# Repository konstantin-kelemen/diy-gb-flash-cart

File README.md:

# FPGA-картридж с Flash-памятью для Game Boy

Экспериментальный USB-программируемый картридж для оригинального Game Boy:
MachXO2-1200HC, NOR Flash MX29LV320E (4 МБ), F-RAM FM28V100 (128 КБ),
RP2040-Zero и преобразователи уровней SN74LVC8T245.

## С чего начать

- [Состояние проекта](docs/STATUS.md) — что реализовано и что проверено.
- [План работ](docs/ROADMAP.md) — следующие этапы и критерии готовности.
- [Документация](docs/README.md) — архитектура, испытания и приоритет источников.
- [Первый обмен USB/SPI](docs/SPI_BRINGUP.md) — подключение стенда и протокол.
- [Запись .gb во Flash](docs/PROGRAMMER.md) — чтение, запись и сравнение ROM.

## Структура репозитория

| Каталог | Содержимое |
|---|---|
| [docs/](docs/README.md) | Проектная документация и журнал испытаний |
| [hardware/](hardware/README.md) | Схемы, PCB и локальные библиотеки KiCad |
| [fpga/](fpga/README.md) | RTL, ограничения, тесты и проект Diamond |
| [firmware/](firmware/README.md) | Прошивки RP2040: SPI-тест и программатор |
| [host/](host/README.md) | Утилита записи и проверки Flash |
| [references/](references/README.md) | Техническая документация и сторонние материалы |
| [releases/](releases/README.md) | Сохранённые сборки и производственные файлы |

Электрические соединения определяет [схема картриджа](hardware/cartridge/cartridge.kicad_sch);
правила сверки приведены в [документации](docs/README.md#приоритет-источников).
Перед работой с памятью см. [режимы и требования безопасности](docs/ARCHITECTURE.md#режимы-работы).

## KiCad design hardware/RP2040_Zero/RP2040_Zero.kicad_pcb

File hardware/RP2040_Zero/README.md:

# Реконструкция Waveshare RP2040-Zero

Отдельный проект KiCad 10: схема и PCB модуля, локальные символы,
посадочные места и таблицы библиотек. `RP2040_Zero.pdf` — сохранённый
исходный материал; `FOOTPRINT_AUDIT.md` — подробности выбора посадочных мест.

Открывать `RP2040_Zero.kicad_pro`. Для стандартных компонентов нужны штатные
библиотеки KiCad. Проект не заменяет основную схему картриджа.

У L1 посадочное место намеренно не назначено: нумерация выводов
WS2812B-2020 расходится с исходной схемой; требуется сверка установленного LED.
P1/P2/P3 обозначают контактные площадки самой платы, а не отдельные разъёмы;
их геометрия должна быть задана при разводке.

Источник схемы: https://files.waveshare.com/upload/4/4c/RP2040_Zero.pdf

Готовность к производству
и результаты ERC/DRC этим проектом не подтверждаются.

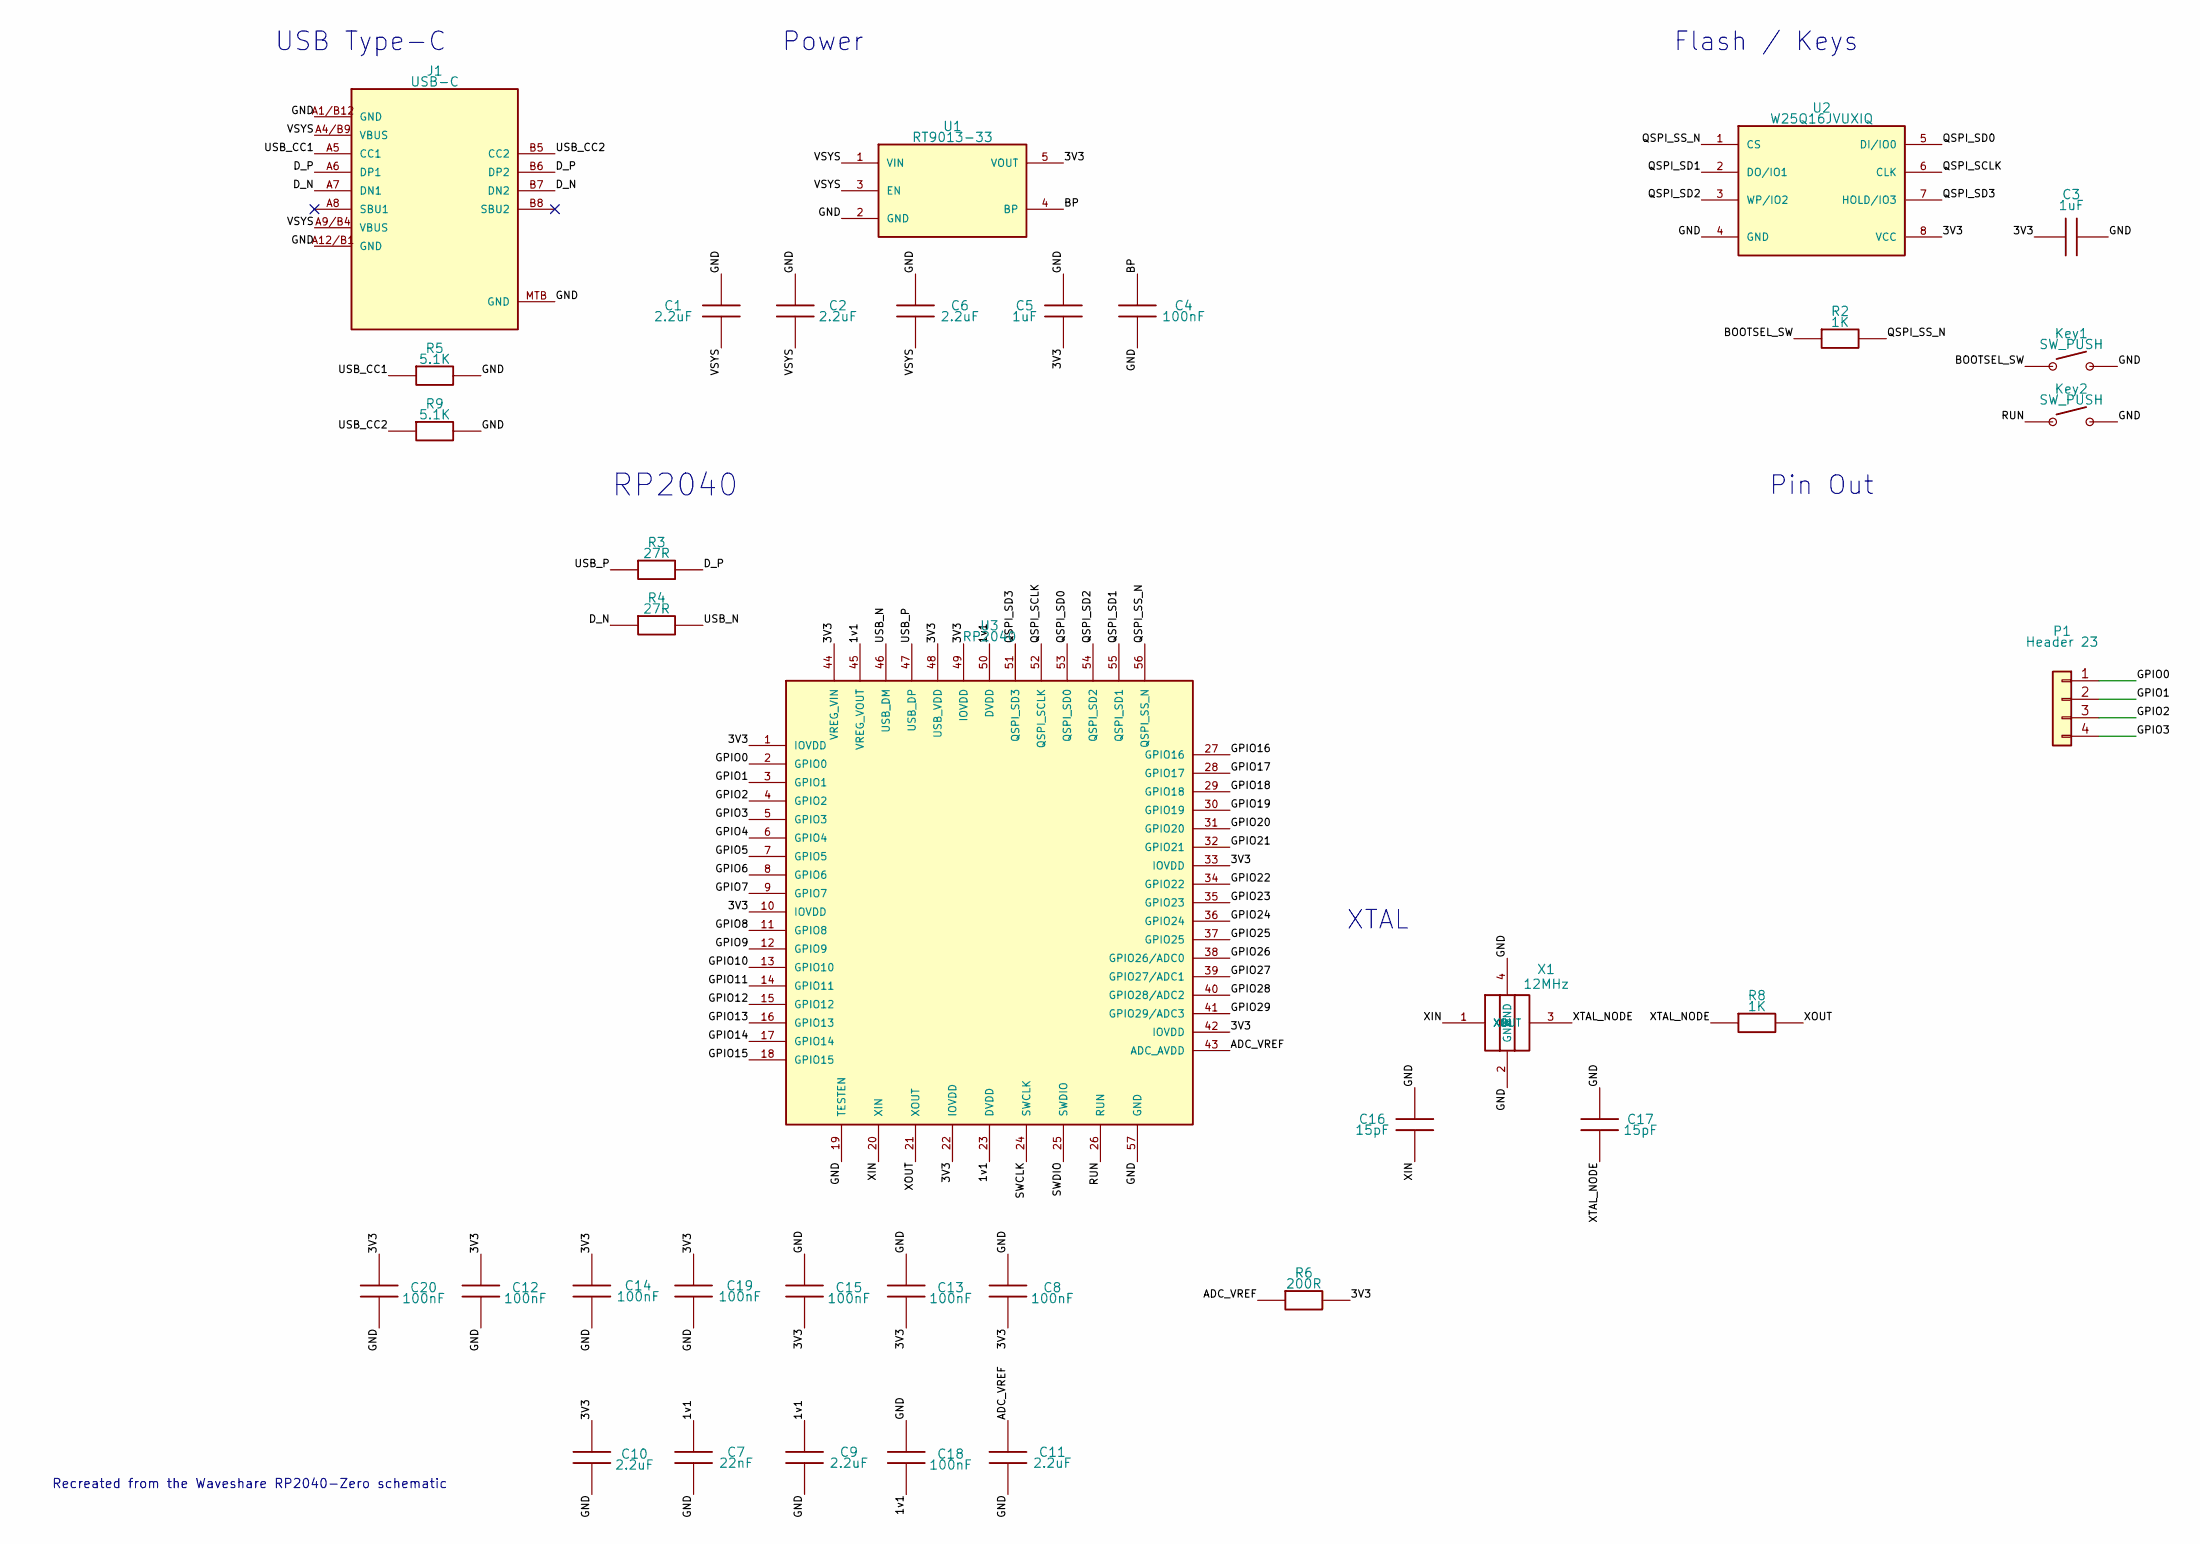
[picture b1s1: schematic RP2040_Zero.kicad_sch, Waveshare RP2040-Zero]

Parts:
C1, C2, C6, C9, C10, C11: 2.2uF; C_0201_0603Metric
C3, C5: 1uF; C_0201_0603Metric
C4, C8, C12, C13, C14, C15, C18, C19, C20: 100nF; C_0201_0603Metric
C7: 22nF; C_0201_0603Metric
C16, C17: 15pF; C_0201_0603Metric
J1: USB-C; USB_C_HRO_TYPE-C-31-M-12_Waveshare
Key1, Key2: SW_PUSH; SW_Tactile_4.5x4.5mm_PhotoMatched
P1: Header 23; PinSocket_1x04_P2.54mm_Vertical
R2, R8: 1K; R_0201_0603Metric
R3, R4: 27R; R_0201_0603Metric
R5, R9: 5.1K; R_0201_0603Metric
R6: 200R; R_0201_0603Metric
U1: RT9013-33; SOT-23-5
U2: W25Q16JVUXIQ; W25Q16JVUXIQ_USON-8_2x3mm
U3: RP2040; QFN-56-1EP_7x7mm_P0.4mm_EP3.2x3.2mm
X1: 12MHz; Crystal_SMD_2520-4Pin_2.5x2.0mm

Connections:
/1v1: C7.1, C9.1, C18.2, U3.23 (DVDD), U3.45 (VREG_VOUT), U3.50 (DVDD)
/3V3: C3.1, C5.2, C8.2, C10.1, C12.1, C13.2, C14.1, C15.2, C19.1, C20.1, R6.2, U1.5 (VOUT), U2.8 (VCC), U3.1 (IOVDD), U3.10 (IOVDD), U3.22 (IOVDD), U3.33 (IOVDD), U3.42 (IOVDD), U3.44 (VREG_VIN), U3.48 (USB_VDD), U3.49 (IOVDD)
/ADC_VREF: C11.1, R6.1, U3.43 (ADC_AVDD)
/BOOTSEL_SW: Key1.1, R2.1
/BP: C4.1, U1.4 (BP)
/D_N: J1.A7 (DN1), J1.B7 (DN2), R4.1
/D_P: J1.A6 (DP1), J1.B6 (DP2), R3.2
/GND: C1.1, C2.1, C3.2, C4.2, C5.1, C6.1, C7.2, C8.1, C9.2, C10.2, C11.2, C12.2, C13.1, C14.2, C15.1, C16.1, C17.1, C18.1, C19.2, C20.2, J1.A1/B12 (GND), J1.A12/B1 (GND), J1.MTB (GND), Key1.2, Key2.2, R5.2, R9.2, U1.2 (GND), U2.4 (GND), U3.19 (TESTEN), U3.57 (GND), X1.2 (GND), X1.4 (GND)
/GPIO0: P1.1, U3.2 (GPIO0)
/GPIO1: P1.2, U3.3 (GPIO1)
/GPIO2: P1.3, U3.4 (GPIO2)
/GPIO3: P1.4, U3.5 (GPIO3)
/GPIO4: U3.6 (GPIO4)
/GPIO5: U3.7 (GPIO5)
/GPIO6: U3.8 (GPIO6)
/GPIO7: U3.9 (GPIO7)
/GPIO8: U3.11 (GPIO8)
/GPIO9: U3.12 (GPIO9)
/GPIO10: U3.13 (GPIO10)
/GPIO11: U3.14 (GPIO11)
/GPIO12: U3.15 (GPIO12)
/GPIO13: U3.16 (GPIO13)
/GPIO14: U3.17 (GPIO14)
/GPIO15: U3.18 (GPIO15)
/GPIO16: U3.27 (GPIO16)
/GPIO17: U3.28 (GPIO17)
/GPIO18: U3.29 (GPIO18)
/GPIO19: U3.30 (GPIO19)
/GPIO20: U3.31 (GPIO20)
/GPIO21: U3.32 (GPIO21)
/GPIO22: U3.34 (GPIO22)
/GPIO23: U3.35 (GPIO23)
/GPIO24: U3.36 (GPIO24)
/GPIO25: U3.37 (GPIO25)
/GPIO26: U3.38 (GPIO26/ADC0)
/GPIO27: U3.39 (GPIO27/ADC1)
/GPIO28: U3.40 (GPIO28/ADC2)
/GPIO29: U3.41 (GPIO29/ADC3)
/QSPI_SCLK: U2.6 (CLK), U3.52 (QSPI_SCLK)
/QSPI_SD0: U2.5 (DI/IO0), U3.53 (QSPI_SD0)
/QSPI_SD1: U2.2 (DO/IO1), U3.55 (QSPI_SD1)
/QSPI_SD2: U2.3 (WP/IO2), U3.54 (QSPI_SD2)
/QSPI_SD3: U2.7 (HOLD/IO3), U3.51 (QSPI_SD3)
/QSPI_SS_N: R2.2, U2.1 (CS), U3.56 (QSPI_SS_N)
/RUN: Key2.1, U3.26 (RUN)
/SWCLK: U3.24 (SWCLK)
/SWDIO: U3.25 (SWDIO)
/USB_CC1: J1.A5 (CC1), R5.1
/USB_CC2: J1.B5 (CC2), R9.1
/USB_N: R4.2, U3.46 (USB_DM)
/USB_P: R3.1, U3.47 (USB_DP)
/VSYS: C1.2, C2.2, C6.2, J1.A4/B9 (VBUS), J1.A9/B4 (VBUS), U1.1 (VIN), U1.3 (EN)
/XIN: C16.2, U3.20 (XIN), X1.1 (XIN)
/XOUT: R8.2, U3.21 (XOUT)
/XTAL_NODE: C17.2, R8.1, X1.3 (XOUT)

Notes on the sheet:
Pin Out
Recreated from the Waveshare RP2040-Zero schematic
XTAL
Flash / Keys
Power
RP2040
USB Type-C

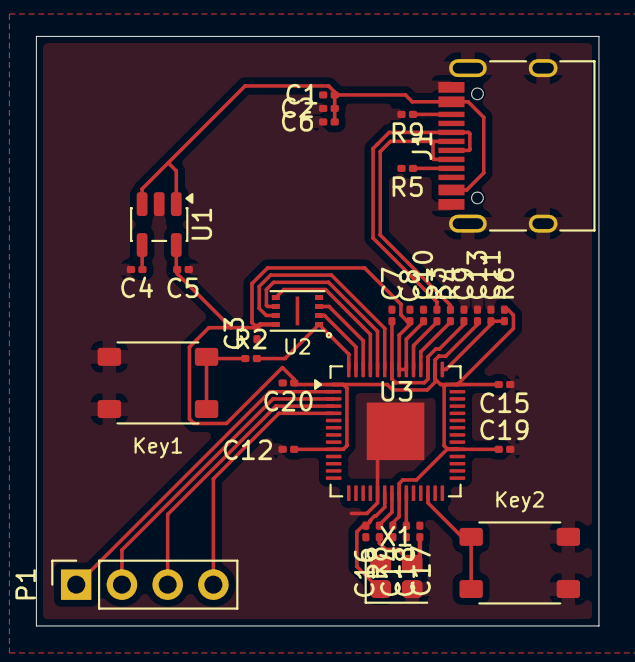
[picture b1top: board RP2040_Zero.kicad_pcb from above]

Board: 2 copper layers, 31.2 x 32.8 mm, 35 parts (0 on the bottom side), 27 nets.

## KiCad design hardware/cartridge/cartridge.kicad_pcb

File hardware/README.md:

# Аппаратная часть

## Проекты

- `breakout/` — разведённая отладочная плата с производственным архивом.
- `cartridge/` — основная схема картриджа и PCB. Состояние разводки — в
  [STATUS.md](../docs/STATUS.md).

- `cartridge/power_mux.kicad_sch` — схема питания; `power_mux_board.kicad_pcb` и
  `power_mux_gerbers/` — отдельная плата и производственные файлы в работе.
- [RP2040_Zero/](RP2040_Zero/README.md) — реконструкция модуля RP2040-Zero.

## Открытие в KiCad

Открывайте `cartridge/cartridge.kicad_pro` или `breakout/breakout.kicad_pro`.
Локальные библиотеки и 3D-модели картриджа хранятся рядом с проектом;
`fp-lib-table` использует пути относительно `${KIPRJMOD}`.
Для стандартных компонентов также нужны штатные библиотеки KiCad.

В `cartridge/sym-lib-table` заданы конкретные файлы локальных символов.

Перед выпуском аппаратной ревизии необходимо выполнить ERC/DRC и сверить LPF с
назначением выводов символа FPGA в схеме.

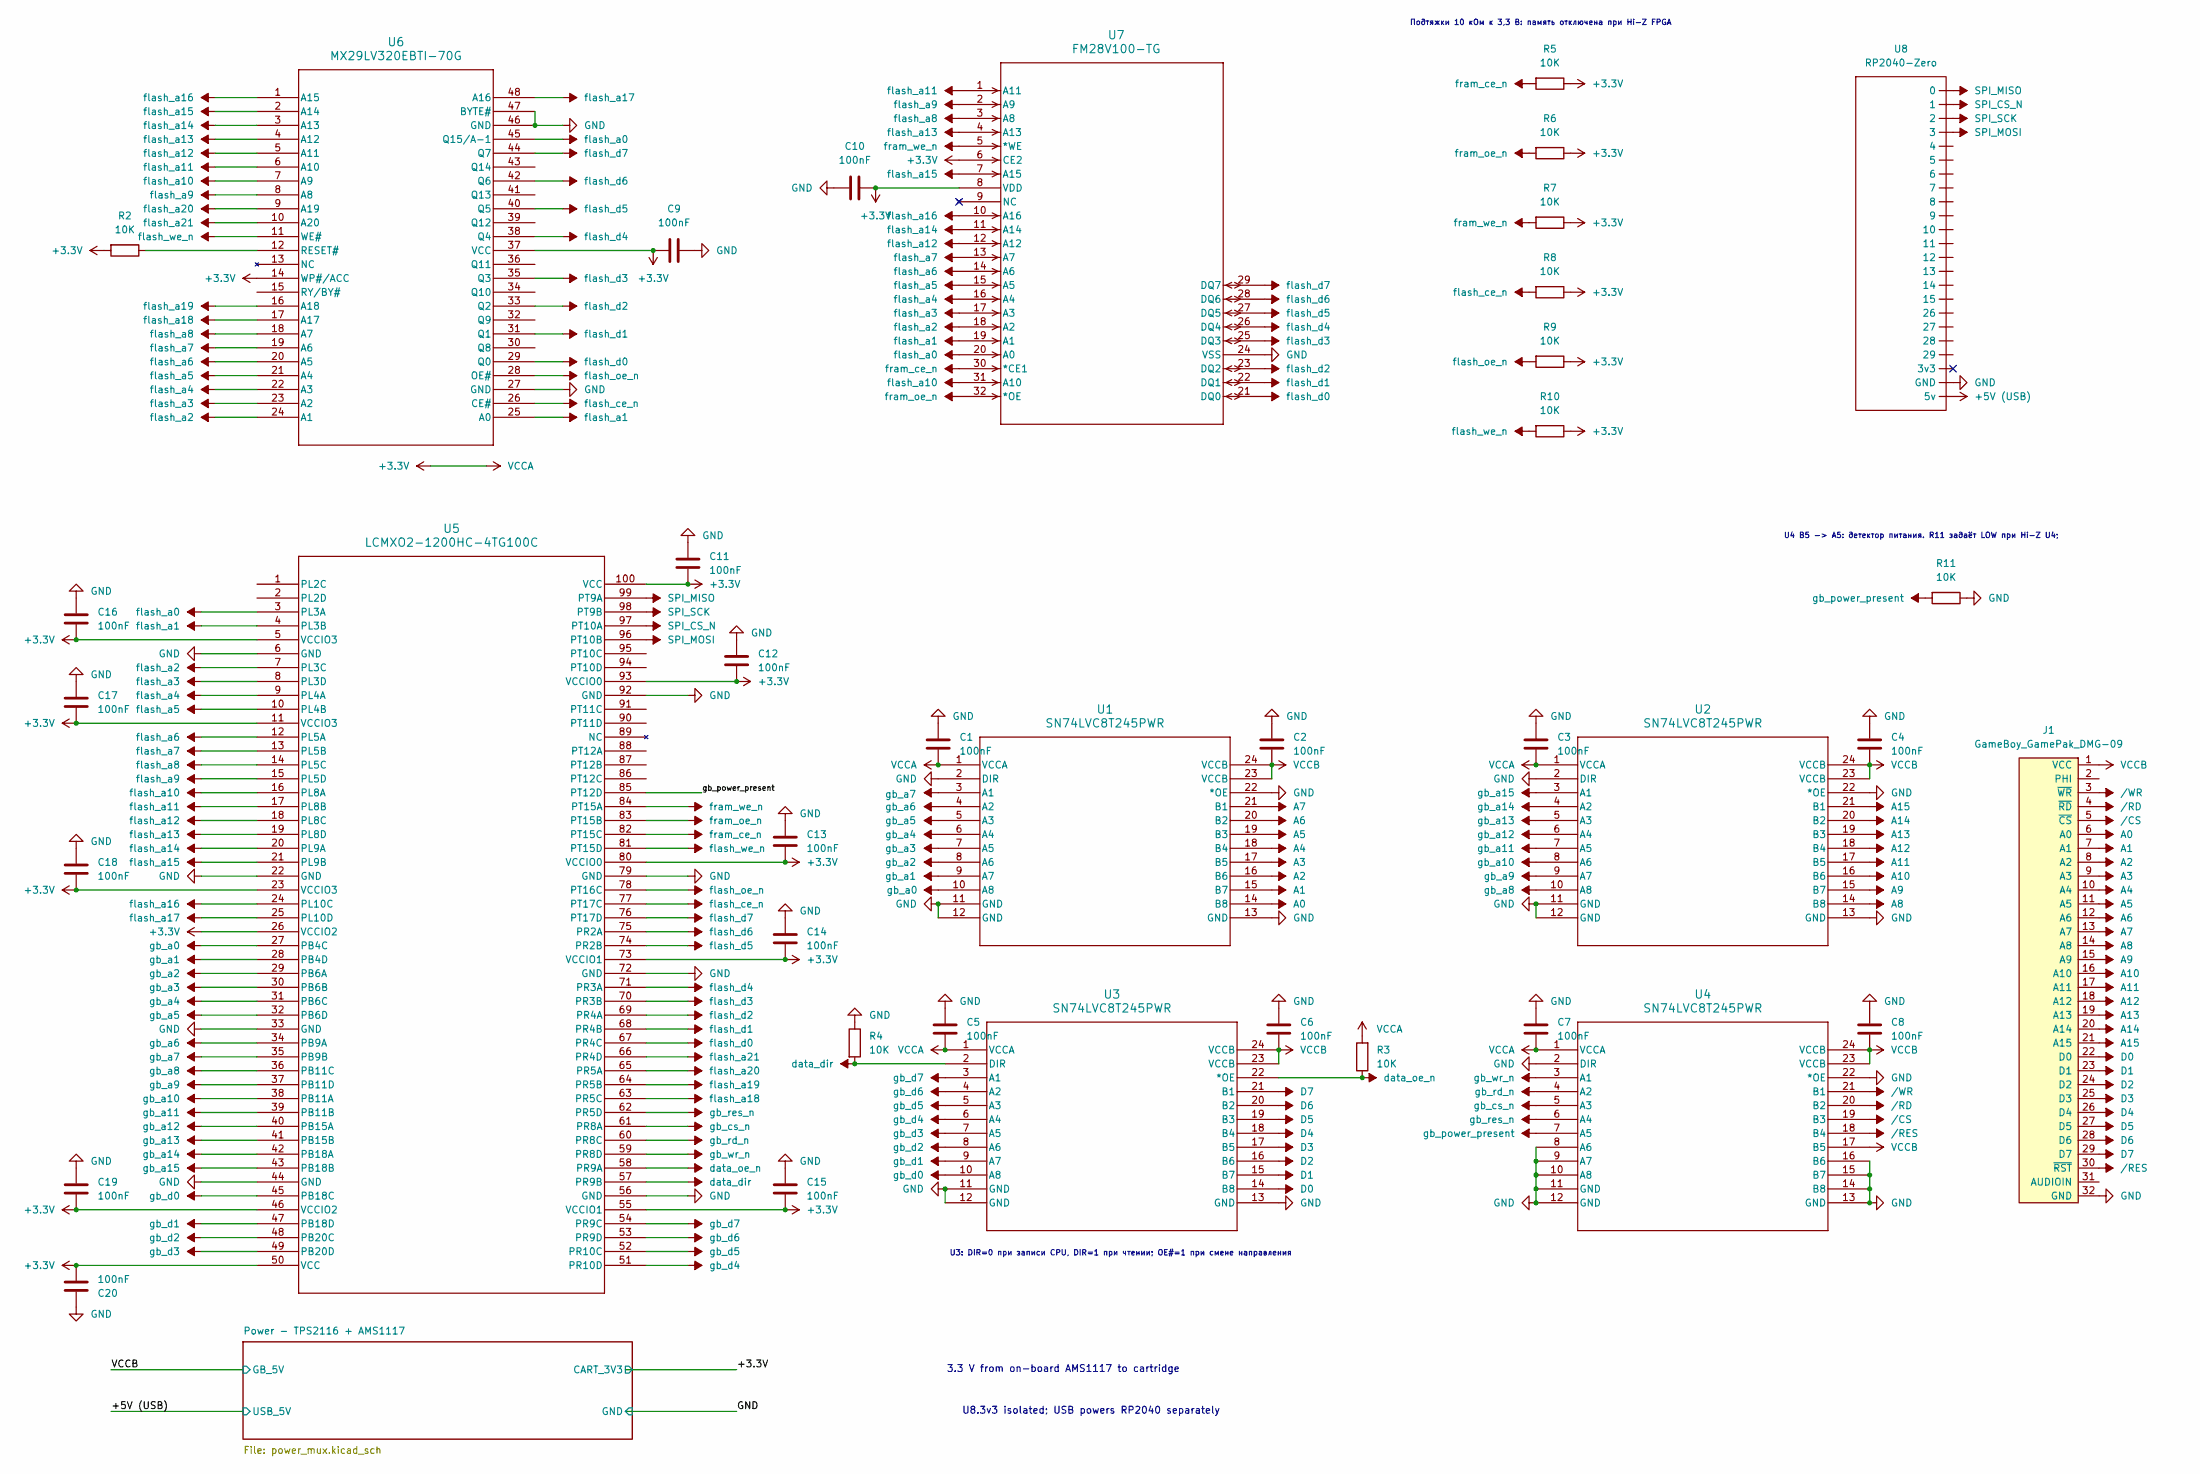
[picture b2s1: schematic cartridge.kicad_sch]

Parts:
C1, C2, C3, C4, C5, C6, C7, C8, C9, C10, C11, C12, C13, C14, C15, C16, C17, C18, C19, C20: 100nF; C_0603_1608Metric_Pad1.08x0.95mm_HandSolder
J1: GameBoy_GamePak_DMG-09; GameBoy_GamePak_DMG-09_P1.50mm_Edge
R2, R3, R4, R5, R6, R7, R8, R9, R10, R11: 10K; R_0603_1608Metric_Pad0.98x0.95mm_HandSolder
U1, U2, U3, U4: SN74LVC8T245PWR; PW24
U5: LCMXO2-1200HC-4TG100C; TQFP100_LAT
U6: MX29LV320EBTI-70G; TSOPI48L12X20NORMAL_MAC
U7: FM28V100-TG; TSOP-32
U8: RP2040-Zero

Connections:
+3.3V: C1.1, C3.1, C5.1, C7.1, C9.1, C10.1, C11.1, C12.1, C13.1, C14.1, C15.1, C16.1, C17.1, C18.1, C19.1, C20.1, R2.2, R3.2, R5.1, R6.1, R7.1, R8.1, R9.1, R10.1, U1.1 (VCCA), U2.1 (VCCA), U3.1 (VCCA), U4.1 (VCCA), U5.5 (VCCIO3), U5.11 (VCCIO3), U5.23 (VCCIO3), U5.26 (VCCIO2), U5.46 (VCCIO2), U5.50 (VCC), U5.55 (VCCIO1), U5.73 (VCCIO1), U5.80 (VCCIO0), U5.93 (VCCIO0), U5.100 (VCC), U6.14 (WP#/ACC), U6.37 (VCC), U7.6 (CE2), U7.8 (VDD); also elsewhere on the board
+5V (USB): U8.5v; also elsewhere on the board
A0: J1.6 (A0), U1.14 (B8)
A1: J1.7 (A1), U1.15 (B7)
A2: J1.8 (A2), U1.16 (B6)
A3: J1.9 (A3), U1.17 (B5)
A4: J1.10 (A4), U1.18 (B4)
A5: J1.11 (A5), U1.19 (B3)
A6: J1.12 (A6), U1.20 (B2)
A7: J1.13 (A7), U1.21 (B1)
A8: J1.14 (A8), U2.14 (B8)
A9: J1.15 (A9), U2.15 (B7)
A10: J1.16 (A10), U2.16 (B6)
A11: J1.17 (A11), U2.17 (B5)
A12: J1.18 (A12), U2.18 (B4)
A13: J1.19 (A13), U2.19 (B3)
A14: J1.20 (A14), U2.20 (B2)
A15: J1.21 (A15), U2.21 (B1)
D0: J1.22 (D0), U3.14 (B8)
D1: J1.23 (D1), U3.15 (B7)
D2: J1.24 (D2), U3.16 (B6)
D3: J1.25 (D3), U3.17 (B5)
D4: J1.26 (D4), U3.18 (B4)
D5: J1.27 (D5), U3.19 (B3)
D6: J1.28 (D6), U3.20 (B2)
D7: J1.29 (D7), U3.21 (B1)
GND: C1.2, C2.2, C3.2, C4.2, C5.2, C6.2, C7.2, C8.2, C9.2, C10.2, C11.2, C12.2, C13.2, C14.2, C15.2, C16.2, C17.2, C18.2, C19.2, C20.2, J1.32 (GND), R4.1, R11.1, U1.2 (DIR), U1.11 (GND), U1.12 (GND), U1.13 (GND), U1.22 (*OE), U2.2 (DIR), U2.11 (GND), U2.12 (GND), U2.13 (GND), U2.22 (*OE), U3.11 (GND), U3.12 (GND), U3.13 (GND), U4.2 (DIR), U4.8 (A6), U4.9 (A7), U4.10 (A8), U4.11 (GND), U4.12 (GND), U4.13 (GND), U4.14 (B8), U4.15 (B7), U4.16 (B6), U4.22 (*OE), U5.6 (GND), U5.22 (GND), U5.33 (GND), U5.44 (GND), U5.56 (GND), U5.72 (GND), U5.79 (GND), U5.92 (GND), U6.27 (GND), U6.46 (GND), U6.47 (BYTE#), U7.24 (VSS), U8.GND; also elsewhere on the board
unnamed: R2.1, U6.12 (RESET#)
SPI_CS_N: U5.97 (PT10A), U8.1
SPI_MISO: U5.99 (PT9A), U8.0
SPI_MOSI: U5.96 (PT10B), U8.3
SPI_SCK: U5.98 (PT9B), U8.2
VCCB: C2.1, C4.1, C6.1, C8.1, J1.1 (VCC), U1.23 (VCCB), U1.24 (VCCB), U2.23 (VCCB), U2.24 (VCCB), U3.23 (VCCB), U3.24 (VCCB), U4.17 (B5), U4.23 (VCCB), U4.24 (VCCB); also elsewhere on the board
data_dir: R4.2, U3.2 (DIR), U5.57 (PR9B)
flash_a0: U5.3 (PL3A), U6.45 (Q15/A-1), U7.20 (A0)
flash_a1: U5.4 (PL3B), U6.25 (A0), U7.19 (A1)
flash_a2: U5.7 (PL3C), U6.24 (A1), U7.18 (A2)
flash_a3: U5.8 (PL3D), U6.23 (A2), U7.17 (A3)
flash_a4: U5.9 (PL4A), U6.22 (A3), U7.16 (A4)
flash_a5: U5.10 (PL4B), U6.21 (A4), U7.15 (A5)
flash_a6: U5.12 (PL5A), U6.20 (A5), U7.14 (A6)
flash_a7: U5.13 (PL5B), U6.19 (A6), U7.13 (A7)
flash_a8: U5.14 (PL5C), U6.18 (A7), U7.3 (A8)
flash_a9: U5.15 (PL5D), U6.8 (A8), U7.2 (A9)
flash_a10: U5.16 (PL8A), U6.7 (A9), U7.31 (A10)
flash_a11: U5.17 (PL8B), U6.6 (A10), U7.1 (A11)
flash_a12: U5.18 (PL8C), U6.5 (A11), U7.12 (A12)
flash_a13: U5.19 (PL8D), U6.4 (A12), U7.4 (A13)
flash_a14: U5.20 (PL9A), U6.3 (A13), U7.11 (A14)
flash_a15: U5.21 (PL9B), U6.2 (A14), U7.7 (A15)
flash_a16: U5.24 (PL10C), U6.1 (A15), U7.10 (A16)
flash_a17: U5.25 (PL10D), U6.48 (A16)
flash_a18: U5.63 (PR5C), U6.17 (A17)
flash_a19: U5.64 (PR5B), U6.16 (A18)
flash_a20: U5.65 (PR5A), U6.9 (A19)
flash_a21: U5.66 (PR4D), U6.10 (A20)
flash_ce_n: R8.2, U5.77 (PT17C), U6.26 (CE#)
flash_d0: U5.67 (PR4C), U6.29 (Q0), U7.21 (DQ0)
flash_d1: U5.68 (PR4B), U6.31 (Q1), U7.22 (DQ1)
flash_d2: U5.69 (PR4A), U6.33 (Q2), U7.23 (DQ2)
flash_d3: U5.70 (PR3B), U6.35 (Q3), U7.25 (DQ3)
flash_d4: U5.71 (PR3A), U6.38 (Q4), U7.26 (DQ4)
flash_d5: U5.74 (PR2B), U6.40 (Q5), U7.27 (DQ5)
flash_d6: U5.75 (PR2A), U6.42 (Q6), U7.28 (DQ6)
flash_d7: U5.76 (PT17D), U6.44 (Q7), U7.29 (DQ7)
flash_oe_n: R9.2, U5.78 (PT16C), U6.28 (OE#)
flash_we_n: R10.2, U5.81 (PT15D), U6.11 (WE#)
fram_ce_n: R5.2, U5.82 (PT15C), U7.30 (*CE1)
fram_oe_n: R6.2, U5.83 (PT15B), U7.32 (*OE)
fram_we_n: R7.2, U5.84 (PT15A), U7.5 (*WE)
gb_a0: U1.10 (A8), U5.27 (PB4C)
gb_a1: U1.9 (A7), U5.28 (PB4D)
gb_a2: U1.8 (A6), U5.29 (PB6A)
gb_a3: U1.7 (A5), U5.30 (PB6B)
gb_a4: U1.6 (A4), U5.31 (PB6C)
gb_a5: U1.5 (A3), U5.32 (PB6D)
gb_a6: U1.4 (A2), U5.34 (PB9A)
gb_a7: U1.3 (A1), U5.35 (PB9B)
gb_a8: U2.10 (A8), U5.36 (PB11C)
gb_a9: U2.9 (A7), U5.37 (PB11D)
gb_a10: U2.8 (A6), U5.38 (PB11A)
gb_a11: U2.7 (A5), U5.39 (PB11B)
gb_a12: U2.6 (A4), U5.40 (PB15A)
gb_a13: U2.5 (A3), U5.41 (PB15B)
gb_a14: U2.4 (A2), U5.42 (PB18A)
gb_a15: U2.3 (A1), U5.43 (PB18B)
gb_cs_n: U4.5 (A3), U5.61 (PR8A)
gb_d0: U3.10 (A8), U5.45 (PB18C)
gb_d1: U3.9 (A7), U5.47 (PB18D)
gb_d2: U3.8 (A6), U5.48 (PB20C)
gb_d3: U3.7 (A5), U5.49 (PB20D)
gb_d4: U3.6 (A4), U5.51 (PR10D)
gb_d5: U3.5 (A3), U5.52 (PR10C)
gb_d6: U3.4 (A2), U5.53 (PR9D)
gb_d7: U3.3 (A1), U5.54 (PR9C)
gb_power_present: R11.2, U4.7 (A5), U5.85 (PT12D)
gb_rd_n: U4.4 (A2), U5.60 (PR8C)
gb_res_n: U4.6 (A4), U5.62 (PR5D)
gb_wr_n: U4.3 (A1), U5.59 (PR8D)
/CS: J1.5 (~CS), U4.19 (B3)
/RD: J1.4 (~RD), U4.20 (B2)
/RES: J1.30 (~RST), U4.18 (B4)
/WR: J1.3 (~WR), U4.21 (B1)

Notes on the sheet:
U3: DIR=0 при записи CPU, DIR=1 при чтении; OE#=1 при смене направления
U4 B5 -> A5: детектор питания. R11 задаёт LOW при Hi-Z U4;
3.3 V from on-board AMS1117 to cartridge
Подтяжки 10 кОм к 3,3 В: память отключена при Hi-Z FPGA
U8.3v3 isolated; USB powers RP2040 separately

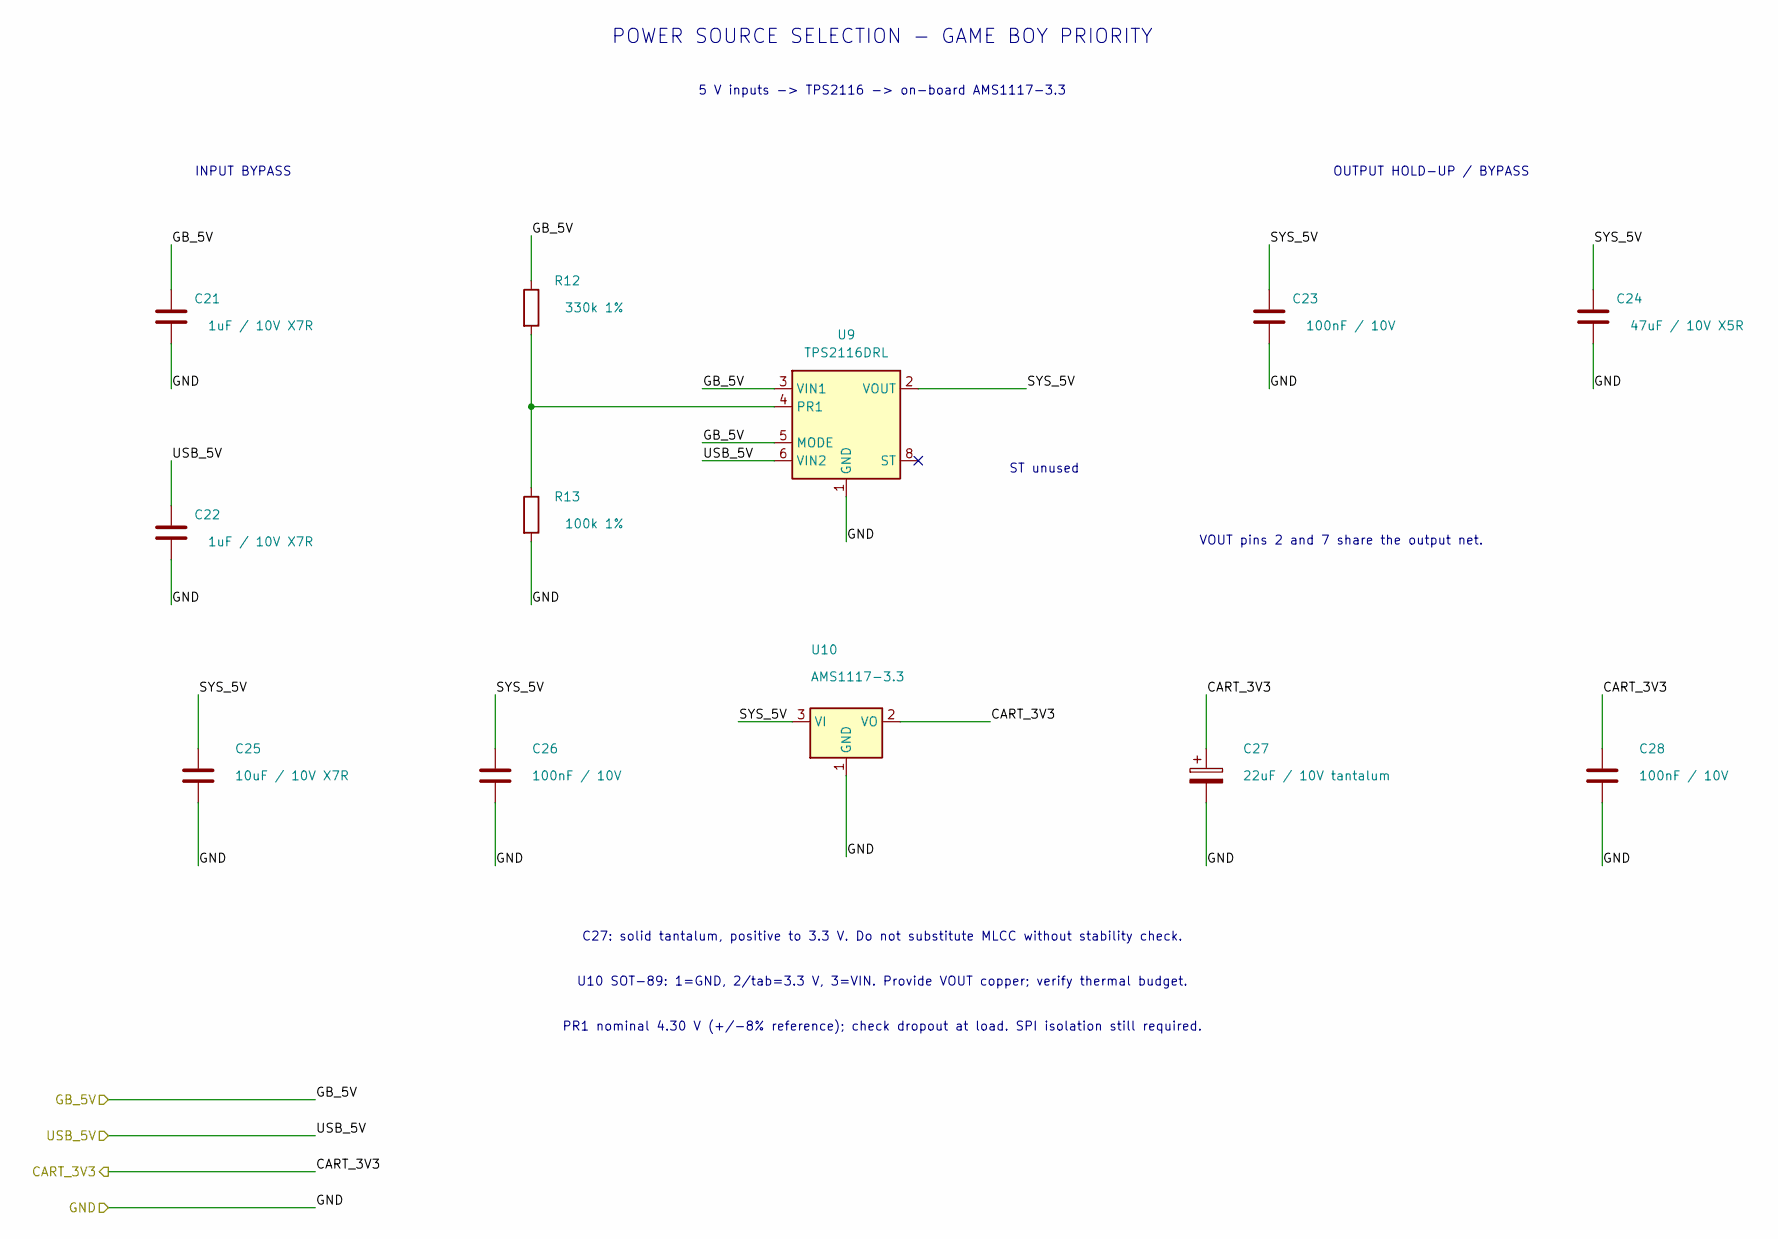
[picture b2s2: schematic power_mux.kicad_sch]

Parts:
C21, C22: 1uF / 10V X7R; C_0805_2012Metric_Pad1.18x1.45mm_HandSolder
C23, C26: 100nF / 10V; C_0603_1608Metric_Pad1.08x0.95mm_HandSolder
C24: 47uF / 10V X5R; C_1210_3225Metric_Pad1.33x2.70mm_HandSolder
C25: 10uF / 10V X7R; C_0805_2012Metric_Pad1.18x1.45mm_HandSolder
C27: 22uF / 10V tantalum; CP_EIA-3528-21_Kemet-B
C28: 100nF / 10V; C_0603_1608Metric
R12: 330k 1%; R_0603_1608Metric_Pad0.98x0.95mm_HandSolder
R13: 100k 1%; R_0603_1608Metric_Pad0.98x0.95mm_HandSolder
U9: TPS2116DRL; SOT-583-8
U10: AMS1117-3.3; SOT-89-3

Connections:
+3.3V: C27.1, C28.1, U10.2 (VO); also elsewhere on the board
+5V (USB): C22.1, U9.6 (VIN2); also elsewhere on the board
/Power - TPS2116 + AMS1117/SYS_5V: C23.1, C24.1, C25.1, C26.1, U9.2 (VOUT), U9.7 (VOUT), U10.3 (VI)
GND: C21.2, C22.2, C23.2, C24.2, C25.2, C26.2, C27.2, C28.2, R13.2, U9.1 (GND), U10.1 (GND); also elsewhere on the board
unnamed: R12.2, R13.1, U9.4 (PR1)
VCCB: C21.1, R12.1, U9.3 (VIN1), U9.5 (MODE); also elsewhere on the board

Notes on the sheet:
ST unused
C27: solid tantalum, positive to 3.3 V. Do not substitute MLCC without stability check.
5 V inputs -> TPS2116 -> on-board AMS1117-3.3
OUTPUT HOLD-UP / BYPASS
POWER SOURCE SELECTION - GAME BOY PRIORITY
U10 SOT-89: 1=GND, 2/tab=3.3 V, 3=VIN. Provide VOUT copper; verify thermal budget.
INPUT BYPASS
VOUT pins 2 and 7 share the output net.
PR1 nominal 4.30 V (+/-8% reference); check dropout at load. SPI isolation still required.

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
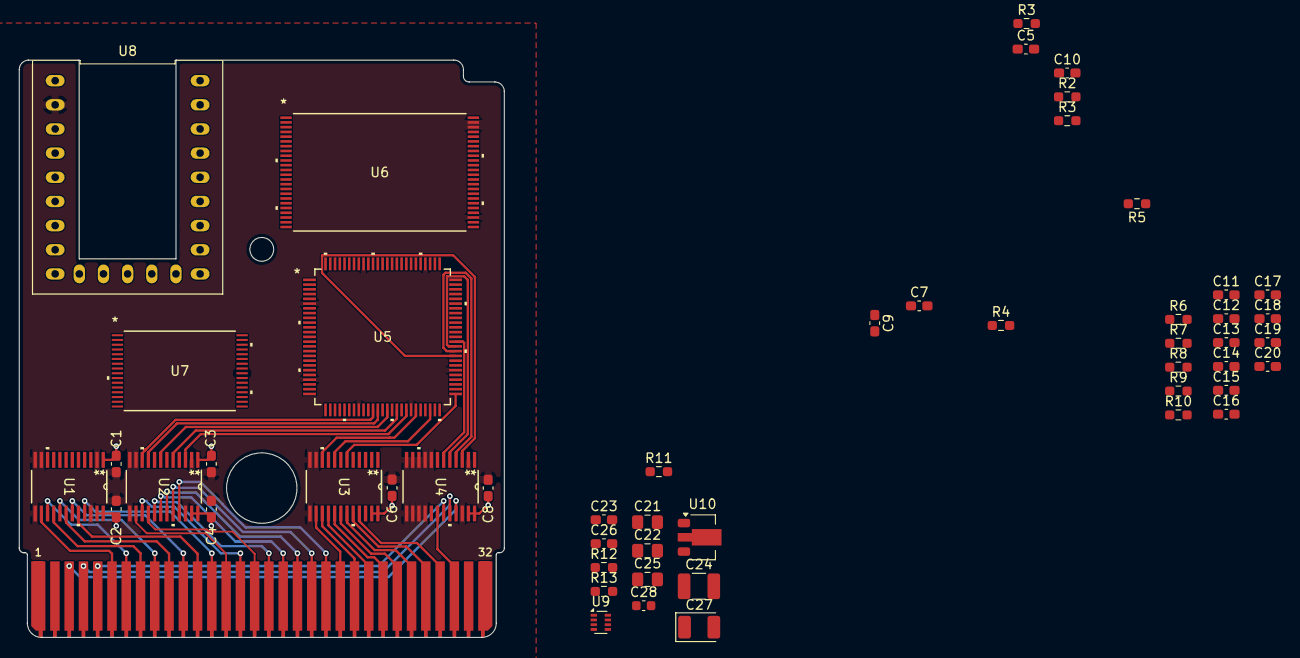
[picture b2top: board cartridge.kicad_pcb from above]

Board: 4 copper layers, 51.0 x 60.7 mm, 52 parts (0 on the bottom side), 106 nets.

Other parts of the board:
R3#2: 10K; R_0603_1608Metric_Pad0.98x0.95mm_HandSolder

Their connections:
+3.3V: R3#2.2; also elsewhere on the board

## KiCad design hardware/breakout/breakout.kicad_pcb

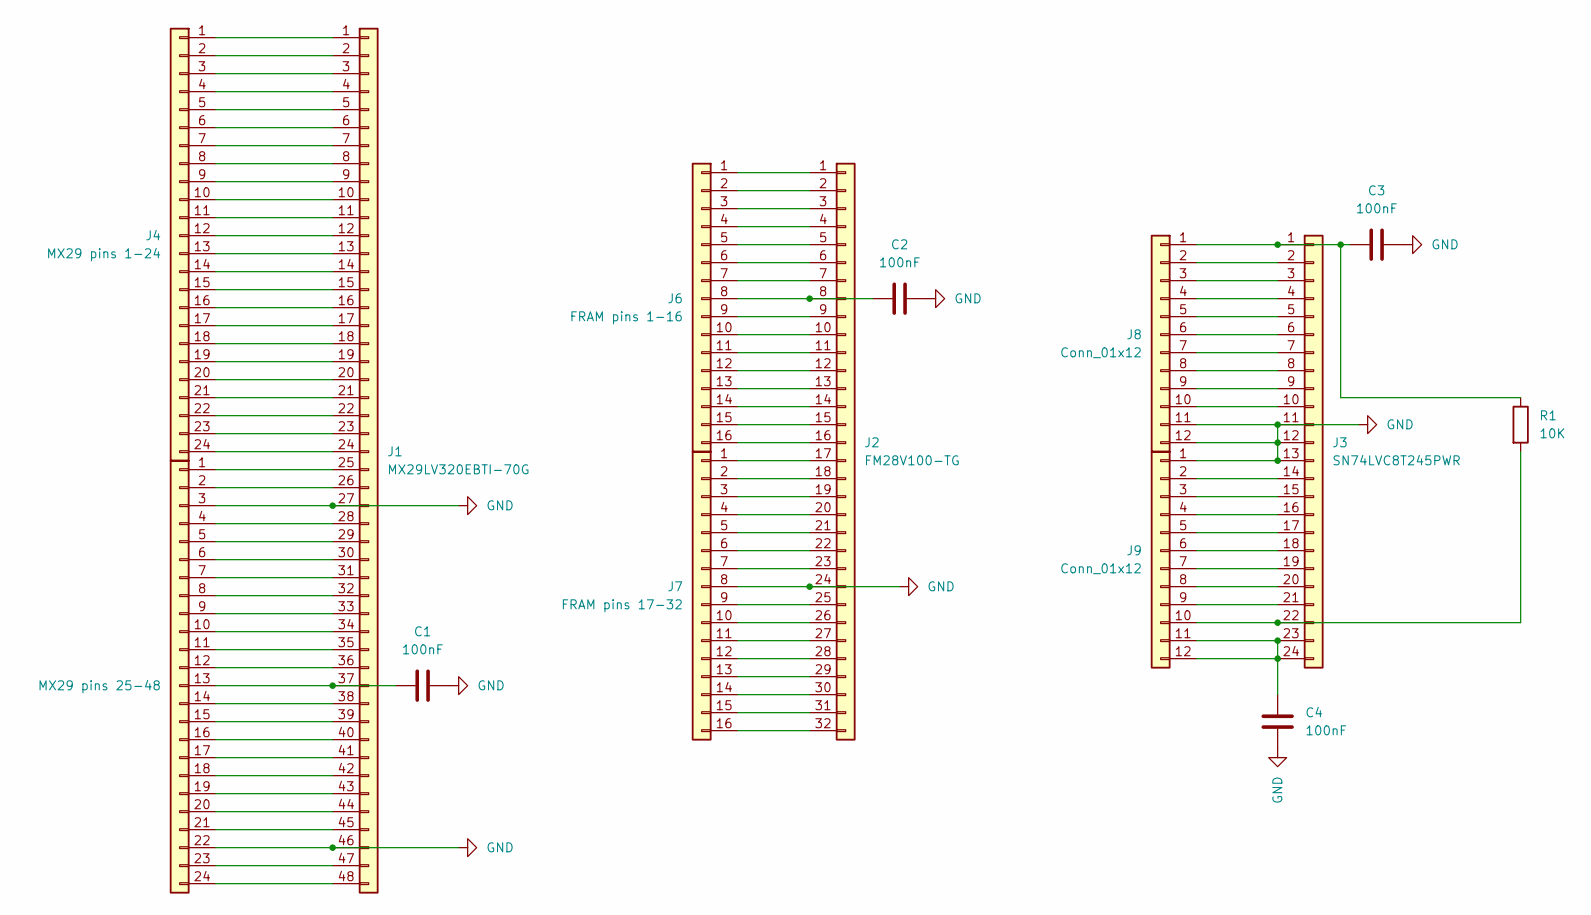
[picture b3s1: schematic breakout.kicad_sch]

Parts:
C1, C2, C3, C4: 100nF; C_0603_1608Metric_Pad1.08x0.95mm_HandSolder
J1: MX29LV320EBTI-70G; TSOP-I-48_18.4x12mm_P0.5mm
J2: FM28V100-TG; TSOP-I-32_11.8x8mm_P0.5mm
J3: SN74LVC8T245PWR; TSSOP-24_4.4x7.8mm_P0.65mm
J4: MX29 pins 1-24; PinHeader_1x24_P2.54mm_Vertical
J5: MX29 pins 25-48; PinHeader_1x24_P2.54mm_Vertical
J6: FRAM pins 1-16; PinHeader_1x16_P2.54mm_Vertical
J7: FRAM pins 17-32; PinHeader_1x16_P2.54mm_Vertical
J8, J9: Conn_01x12; PinHeader_1x12_P2.54mm_Vertical
R1: 10K; R_0603_1608Metric_Pad0.98x0.95mm_HandSolder

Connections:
GND: C1.2, C2.2, C3.2, C4.2, J1.27, J1.46, J2.24, J3.11, J3.12, J3.13, J5.3, J5.22, J7.8, J8.11, J8.12, J9.1
unnamed: J1.1, J4.1
unnamed: J1.2, J4.2
unnamed: J1.3, J4.3
unnamed: J1.4, J4.4
unnamed: J1.5, J4.5
unnamed: J1.6, J4.6
unnamed: J1.7, J4.7
unnamed: J1.8, J4.8
unnamed: J1.9, J4.9
unnamed: J1.10, J4.10
unnamed: J1.11, J4.11
unnamed: J1.12, J4.12
unnamed: J1.13, J4.13
unnamed: J1.14, J4.14
unnamed: J1.15, J4.15
unnamed: J1.16, J4.16
unnamed: J1.17, J4.17
unnamed: J1.18, J4.18
unnamed: J1.19, J4.19
unnamed: J1.20, J4.20
unnamed: J1.21, J4.21
unnamed: J1.22, J4.22
unnamed: J1.23, J4.23
unnamed: J1.24, J4.24
unnamed: J1.25, J5.1
unnamed: J1.26, J5.2
unnamed: J1.28, J5.4
unnamed: J1.29, J5.5
unnamed: J1.30, J5.6
unnamed: J1.31, J5.7
unnamed: J1.32, J5.8
unnamed: J1.33, J5.9
unnamed: J1.34, J5.10
unnamed: J1.35, J5.11
unnamed: J1.36, J5.12
unnamed: C1.1, J1.37, J5.13
unnamed: J1.38, J5.14
unnamed: J1.39, J5.15
unnamed: J1.40, J5.16
unnamed: J1.41, J5.17
unnamed: J1.42, J5.18
unnamed: J1.43, J5.19
unnamed: J1.44, J5.20
unnamed: J1.45, J5.21
unnamed: J1.47, J5.23
unnamed: J1.48, J5.24
unnamed: J2.1, J6.1
unnamed: J2.2, J6.2
unnamed: J2.3, J6.3
unnamed: J2.4, J6.4
unnamed: J2.5, J6.5
unnamed: J2.6, J6.6
unnamed: J2.7, J6.7
unnamed: C2.1, J2.8, J6.8
unnamed: J2.9, J6.9
unnamed: J2.10, J6.10
unnamed: J2.11, J6.11
unnamed: J2.12, J6.12
unnamed: J2.13, J6.13
unnamed: J2.14, J6.14
unnamed: J2.15, J6.15
unnamed: J2.16, J6.16
unnamed: J2.17, J7.1
unnamed: J2.18, J7.2
unnamed: J2.19, J7.3
unnamed: J2.20, J7.4
unnamed: J2.21, J7.5
unnamed: J2.22, J7.6
unnamed: J2.23, J7.7
unnamed: J2.25, J7.9
unnamed: J2.26, J7.10
unnamed: J2.27, J7.11
unnamed: J2.28, J7.12
unnamed: J2.29, J7.13
unnamed: J2.30, J7.14
unnamed: J2.31, J7.15
unnamed: J2.32, J7.16
unnamed: C3.1, J3.1, J8.1, R1.1
unnamed: J3.2, J8.2
unnamed: J3.3, J8.3
unnamed: J3.4, J8.4
unnamed: J3.5, J8.5
unnamed: J3.6, J8.6
unnamed: J3.7, J8.7
unnamed: J3.8, J8.8
unnamed: J3.9, J8.9
unnamed: J3.10, J8.10
unnamed: J3.14, J9.2
unnamed: J3.15, J9.3
unnamed: J3.16, J9.4
unnamed: J3.17, J9.5
unnamed: J3.18, J9.6
unnamed: J3.19, J9.7
unnamed: J3.20, J9.8
unnamed: J3.21, J9.9
unnamed: J3.22, J9.10, R1.2
unnamed: C4.1, J3.23, J3.24, J9.11, J9.12

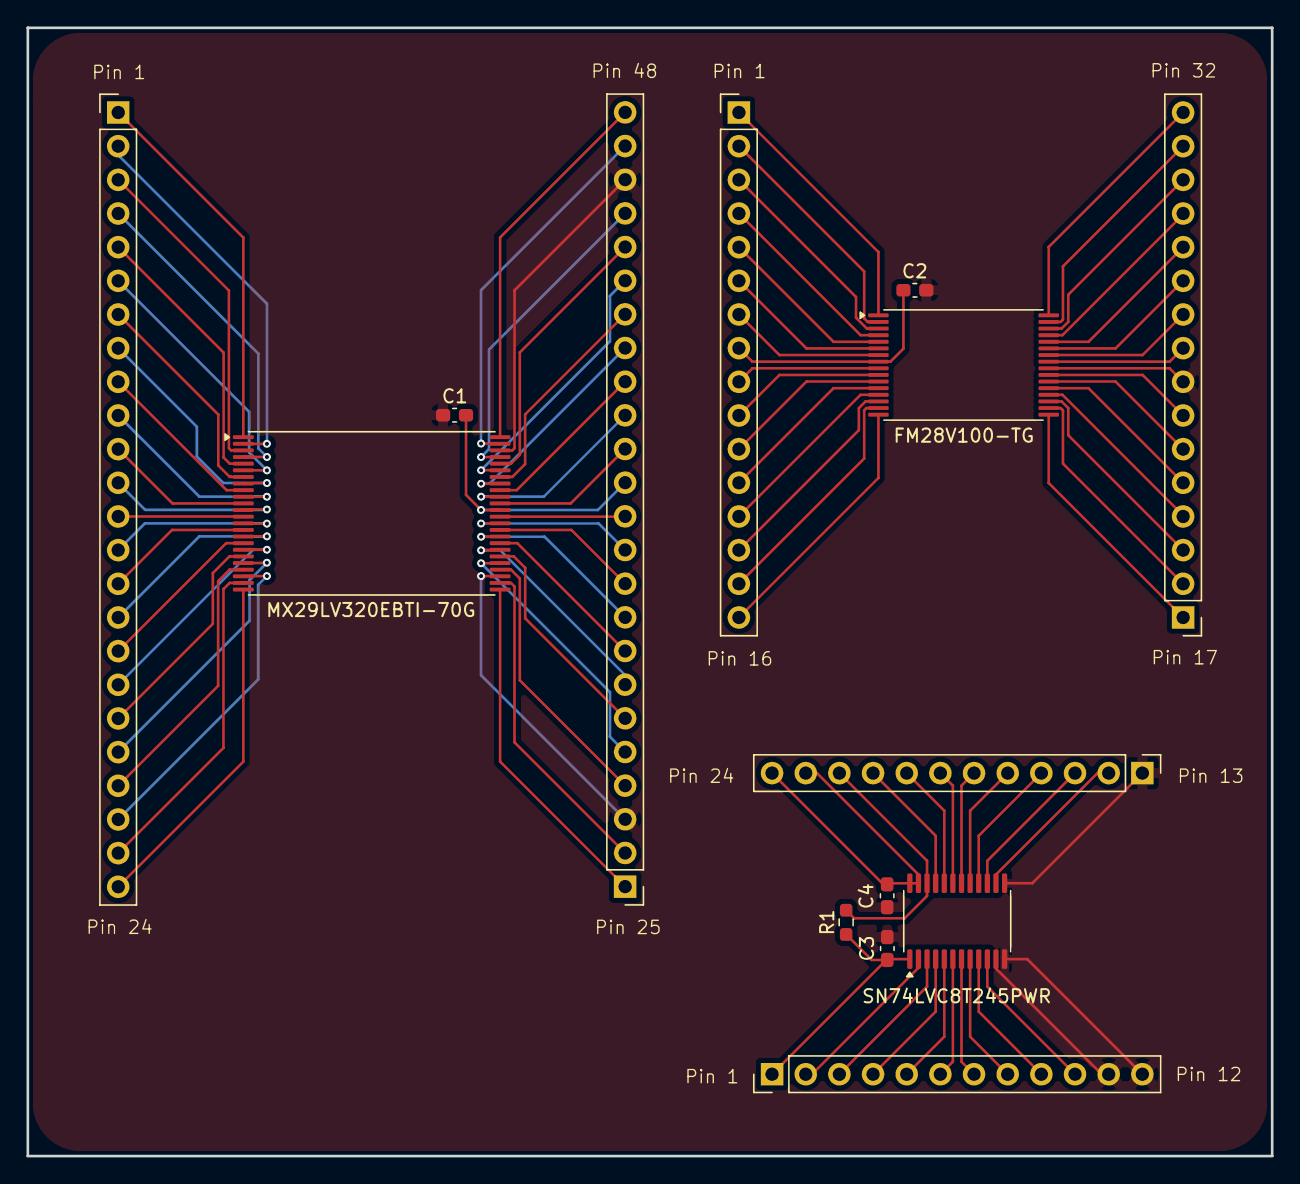
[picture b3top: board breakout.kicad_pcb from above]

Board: 2 copper layers, 93.9 x 85.1 mm, 14 parts (0 on the bottom side), 98 nets.

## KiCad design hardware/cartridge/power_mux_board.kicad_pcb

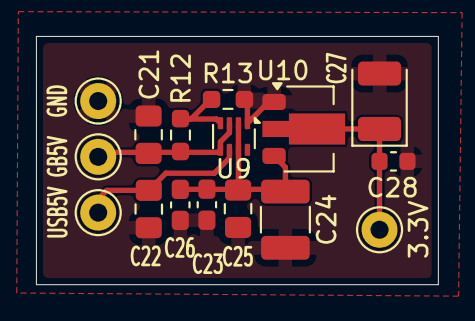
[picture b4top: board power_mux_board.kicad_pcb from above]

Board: 2 copper layers, 22.3 x 13.8 mm, 16 parts (0 on the bottom side), 6 nets.

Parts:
3.3V: Pin_D1.0mm_L10.0mm
C21, C22: 1uF / 10V X7R; C_0805_2012Metric_Pad1.18x1.45mm_HandSolder
C23, C26: 100nF / 10V; C_0603_1608Metric_Pad1.08x0.95mm_HandSolder
C24: 47uF / 10V X5R; C_1210_3225Metric_Pad1.33x2.70mm_HandSolder
C25: 10uF / 10V X7R; C_0805_2012Metric_Pad1.18x1.45mm_HandSolder
C27: 22uF / 10V tantalum; CP_EIA-3528-21_Kemet-B
C28: 100nF / 10V; C_0603_1608Metric
GB5V: Pin_D1.0mm_L10.0mm
GND: Pin_D1.0mm_L10.0mm
R12: 330k 1%; R_0603_1608Metric_Pad0.98x0.95mm_HandSolder
R13: 100k 1%; R_0603_1608Metric_Pad0.98x0.95mm_HandSolder
U9: TPS2116DRL; SOT-583-8
U10: AMS1117-3.3; SOT-89-3
USB5V: Pin_D1.0mm_L10.0mm

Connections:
+3.3V: 3.3V.1, C27.1, C28.1, U10.2 (VO)
+5V (USB): C22.1, U9.6 (VIN2), USB5V.1
/Power - TPS2116 + AMS1117/SYS_5V: C23.1, C24.1, C25.1, C26.1, U9.2 (VOUT), U9.7 (VOUT), U10.3 (VI)
GND: C21.2, C22.2, C23.2, C24.2, C25.2, C26.2, C27.2, C28.2, GND.1, R13.2, U9.1 (GND), U10.1 (GND)
unnamed: R12.2, R13.1, U9.4 (PR1)
VCCB: C21.1, GB5V.1, R12.1, U9.3 (VIN1), U9.5 (MODE)
